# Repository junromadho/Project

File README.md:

Project
=======

It contains jun romadho's project free to share

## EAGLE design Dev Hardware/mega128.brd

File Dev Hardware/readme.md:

ini project bebas, temanya development board atmega128

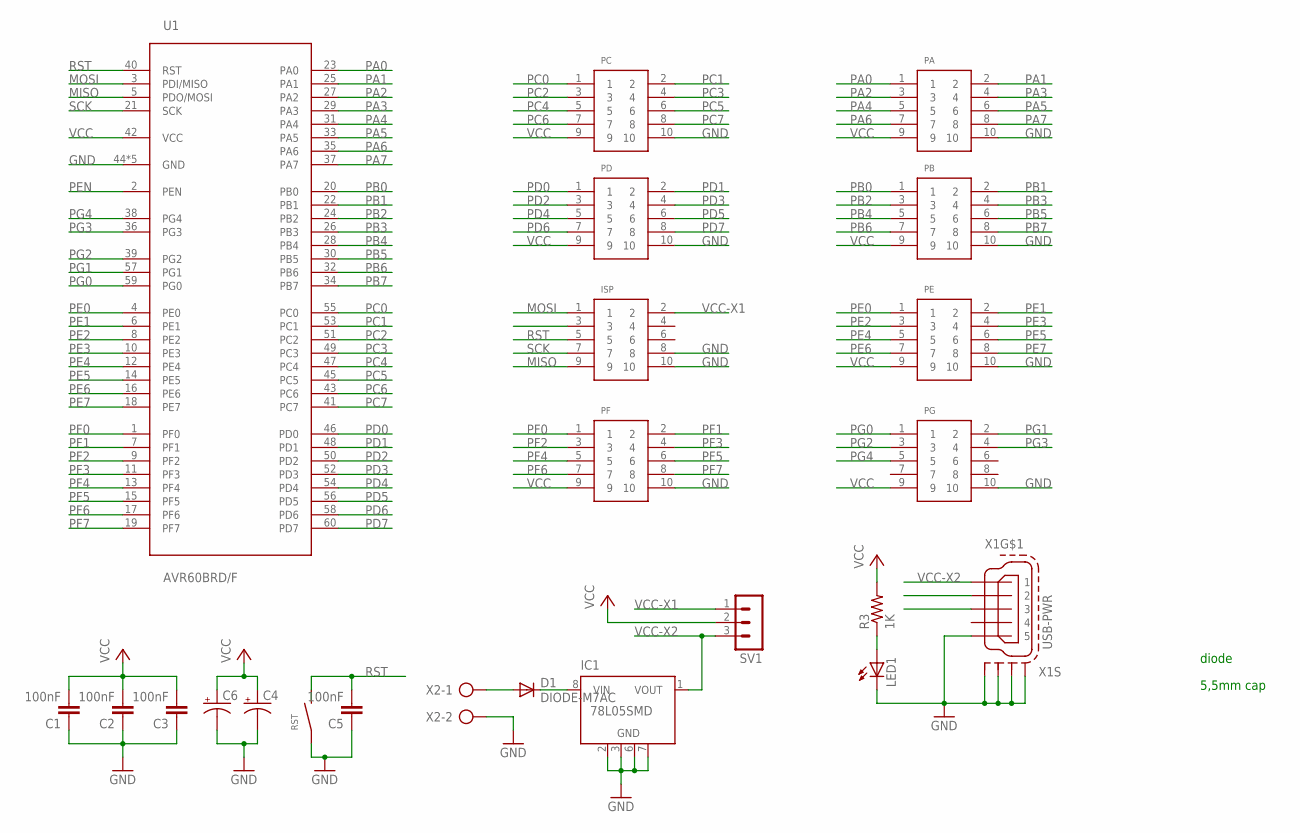
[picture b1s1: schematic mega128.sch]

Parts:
C1, C2, C3, C5: 100nF; C0805
C4, C6: CPOL-US085CS-1AR; 085CS_1AR
D1: DIODE-M7AC; M7
IC1: 78L05SMD; SO08
ISP: IDC-SOCK
LED1: LEDSML0805; SML0805
PA: IDC-SOCK
PB: IDC-SOCK
PC: IDC-SOCK
PD: IDC-SOCK
PE: IDC-SOCK
PF: IDC-SOCK
PG: IDC-SOCK
R3: 1K; R0805
RST: SMD-BTN
SV1: MA03-1
U1: AVR60BRD/F; AVR60-BRD
X1: USB-PWR; 32005-201
X2: AK300/2

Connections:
GND: C1.1, C2.1, C3.1, C4.-, C5.1, C6.-, IC1.2 (GND), IC1.3 (GND), IC1.6 (GND), IC1.7 (GND), ISP.8, ISP.10, LED1.C, PA.10, PB.10, PC.10, PD.10, PE.10, PF.10, PG.10, RST.1, U1.44 (GND), U1.61 (GND), U1.62 (GND), U1.63 (GND), U1.64 (GND), X1.5, X1.M1 (S1), X1.M2 (S2), X1.M3 (S3), X1.M4 (S4), X2.2
MISO: ISP.9, U1.5 (PDO/MOSI)
MOSI: ISP.1, U1.3 (PDI/MISO)
unnamed: LED1.A, R3.1
unnamed: D1.2 (A), X2.1
unnamed: D1.1 (C), IC1.8 (VIN)
PA0: PA.1, U1.23 (PA0)
PA1: PA.2, U1.25 (PA1)
PA2: PA.3, U1.27 (PA2)
PA3: PA.4, U1.29 (PA3)
PA4: PA.5, U1.31 (PA4)
PA5: PA.6, U1.33 (PA5)
PA6: PA.7, U1.35 (PA6)
PA7: PA.8, U1.37 (PA7)
PB0: PB.1, U1.20 (PB0)
PB1: PB.2, U1.22 (PB1)
PB2: PB.3, U1.24 (PB2)
PB3: PB.4, U1.26 (PB3)
PB4: PB.5, U1.28 (PB4)
PB5: PB.6, U1.30 (PB5)
PB6: PB.7, U1.32 (PB6)
PB7: PB.8, U1.34 (PB7)
PC0: PC.1, U1.55 (PC0)
PC1: PC.2, U1.53 (PC1)
PC2: PC.3, U1.51 (PC2)
PC3: PC.4, U1.49 (PC3)
PC4: PC.5, U1.47 (PC4)
PC5: PC.6, U1.45 (PC5)
PC6: PC.7, U1.43 (PC6)
PC7: PC.8, U1.41 (PC7)
PD0: PD.1, U1.46 (PD0)
PD1: PD.2, U1.48 (PD1)
PD2: PD.3, U1.50 (PD2)
PD3: PD.4, U1.52 (PD3)
PD4: PD.5, U1.54 (PD4)
PD5: PD.6, U1.56 (PD5)
PD6: PD.7, U1.58 (PD6)
PD7: PD.8, U1.60 (PD7)
PE0: PE.1, U1.4 (PE0)
PE1: PE.2, U1.6 (PE1)
PE2: PE.3, U1.8 (PE2)
PE3: PE.4, U1.10 (PE3)
PE4: PE.5, U1.12 (PE4)
PE5: PE.6, U1.14 (PE5)
PE6: PE.7, U1.16 (PE6)
PE7: PE.8, U1.18 (PE7)
PEN: U1.2 (PEN)
PF0: PF.1, U1.1 (PF0)
PF1: PF.2, U1.7 (PF1)
PF2: PF.3, U1.9 (PF2)
PF3: PF.4, U1.11 (PF3)
PF4: PF.5, U1.13 (PF4)
PF5: PF.6, U1.15 (PF5)
PF6: PF.7, U1.17 (PF6)
PF7: PF.8, U1.19 (PF7)
PG0: PG.1, U1.59 (PG0)
PG1: PG.2, U1.57 (PG1)
PG2: PG.3, U1.39 (PG2)
PG3: PG.4, U1.36 (PG3)
PG4: PG.5, U1.38 (PG4)
RST: C5.2, ISP.5, RST.2, U1.40 (RST)
SCK: ISP.7, U1.21 (SCK)
VCC: C1.2, C2.2, C3.2, C4.+, C6.+, PA.9, PB.9, PC.9, PD.9, PE.9, PF.9, PG.9, R3.2, SV1.2, U1.42 (VCC)
VCC-X1: ISP.2, SV1.1
VCC-X2: IC1.1 (VOUT), SV1.3, X1.1

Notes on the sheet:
5,5mm cap
diode

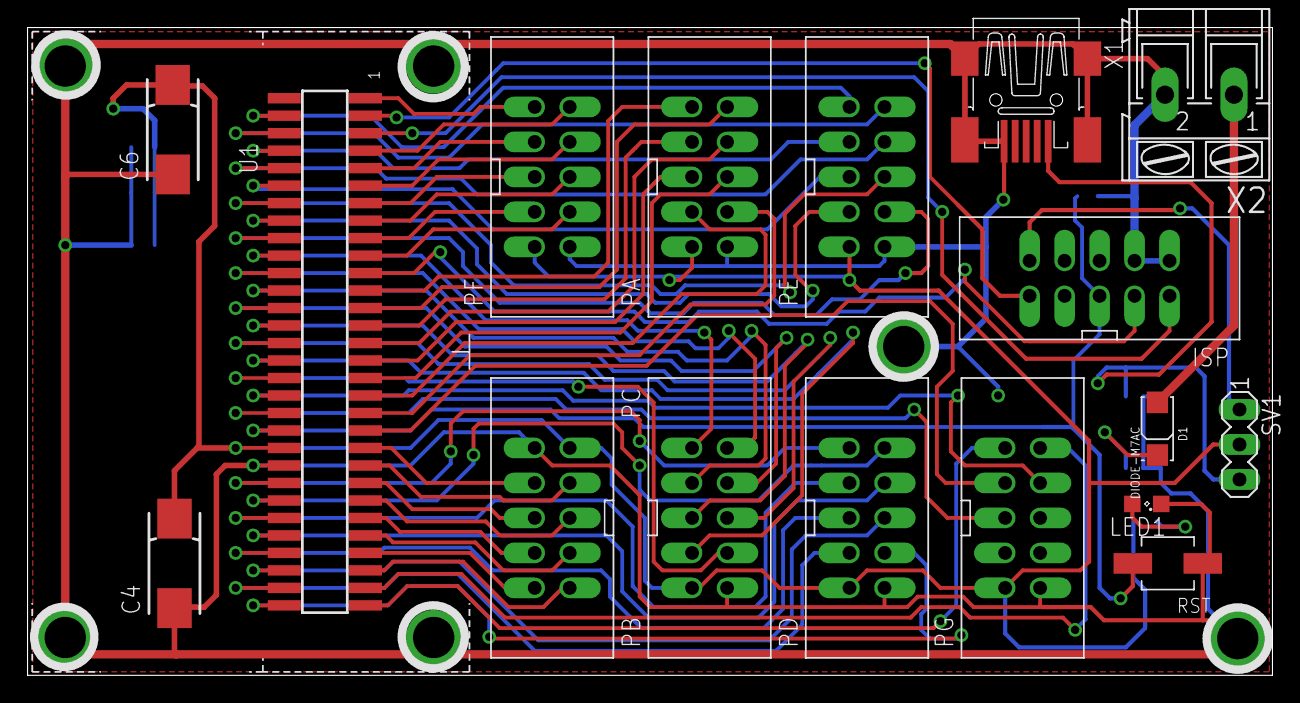
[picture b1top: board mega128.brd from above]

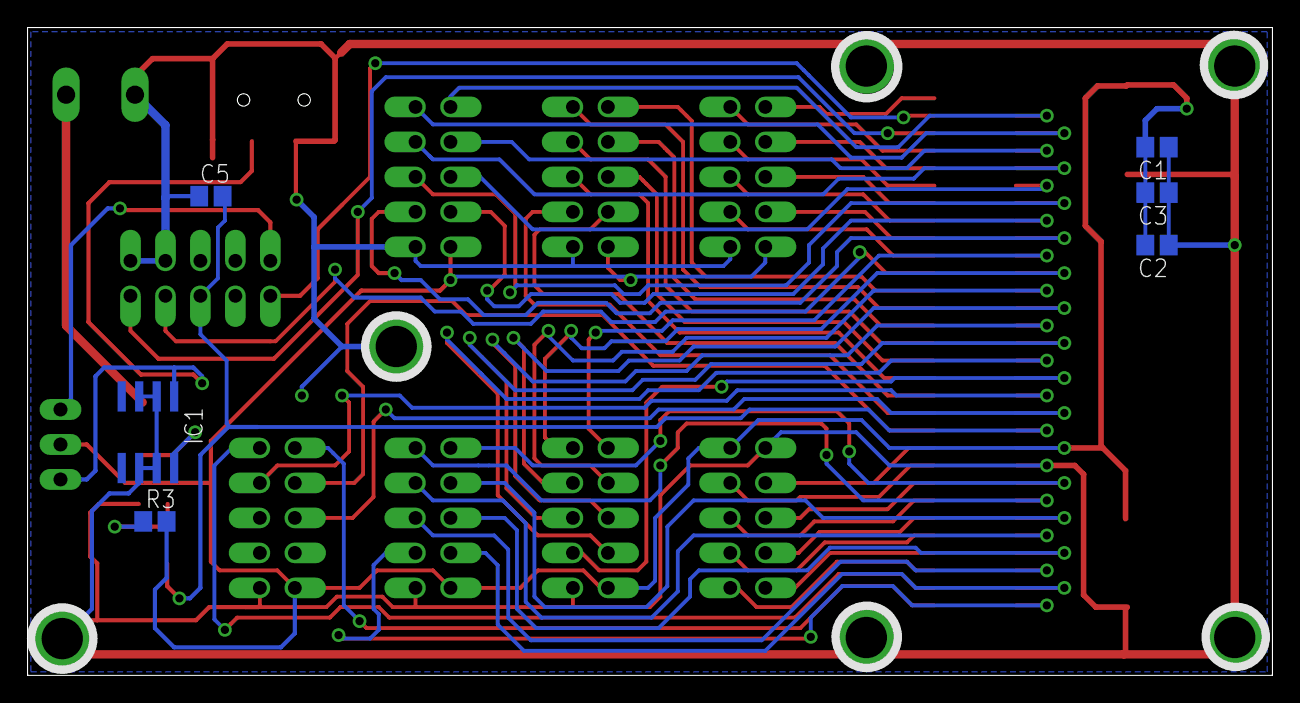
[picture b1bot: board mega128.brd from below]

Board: 2 copper layers, 90.4 x 47.0 mm, 23 parts (6 on the bottom side), 64 nets.

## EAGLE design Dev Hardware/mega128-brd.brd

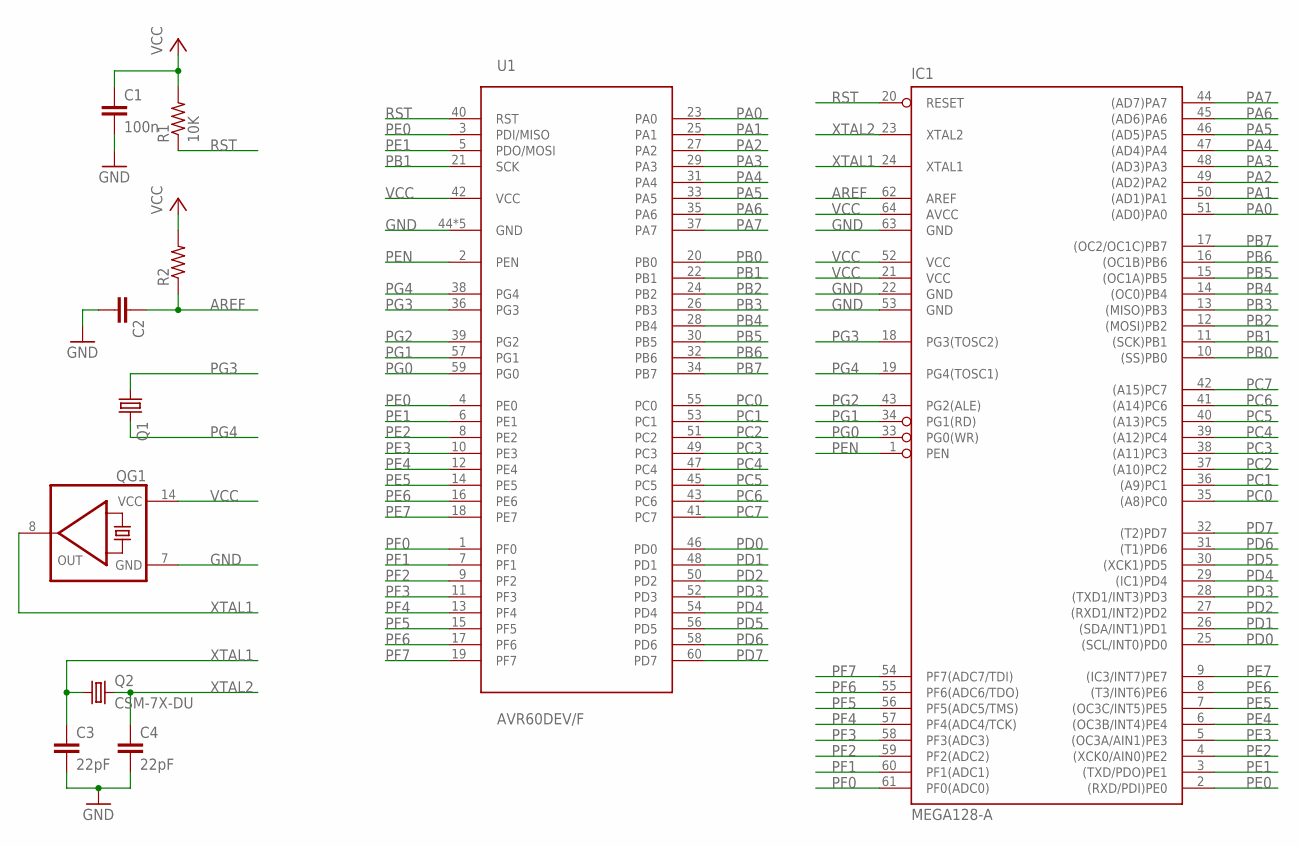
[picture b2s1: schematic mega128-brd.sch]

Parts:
C1: 100n; C0805
C2: C-EUC0805; C0805
C3, C4: 22pF; C0805
IC1: MEGA128-A; TQFP64
Q1: CRYSTALTC26V; TC26V
Q2: CSM-7X-DU
QG1: QG5860; DIL14S
R1: 10K; R0805
R2: R-US_R0805; R0805
U1: AVR60DEV/F; AVR60-DEV

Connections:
AREF: C2.1, IC1.62 (AREF), R2.1
GND: C1.2, C2.2, C3.2, C4.2, IC1.22 (GND), IC1.53 (GND), IC1.63 (GND), QG1.7 (GND), U1.44 (GND), U1.61 (GND), U1.62 (GND), U1.63 (GND), U1.64 (GND)
PA0: IC1.51 ((AD0)PA0), U1.23 (PA0)
PA1: IC1.50 ((AD1)PA1), U1.25 (PA1)
PA2: IC1.49 ((AD2)PA2), U1.27 (PA2)
PA3: IC1.48 ((AD3)PA3), U1.29 (PA3)
PA4: IC1.47 ((AD4)PA4), U1.31 (PA4)
PA5: IC1.46 ((AD5)PA5), U1.33 (PA5)
PA6: IC1.45 ((AD6)PA6), U1.35 (PA6)
PA7: IC1.44 ((AD7)PA7), U1.37 (PA7)
PB0: IC1.10 ((SS)PB0), U1.20 (PB0)
PB1: IC1.11 ((SCK)PB1), U1.21 (SCK), U1.22 (PB1)
PB2: IC1.12 ((MOSI)PB2), U1.24 (PB2)
PB3: IC1.13 ((MISO)PB3), U1.26 (PB3)
PB4: IC1.14 ((OC0)PB4), U1.28 (PB4)
PB5: IC1.15 ((OC1A)PB5), U1.30 (PB5)
PB6: IC1.16 ((OC1B)PB6), U1.32 (PB6)
PB7: IC1.17 ((OC2/OC1C)PB7), U1.34 (PB7)
PC0: IC1.35 ((A8)PC0), U1.55 (PC0)
PC1: IC1.36 ((A9)PC1), U1.53 (PC1)
PC2: IC1.37 ((A10)PC2), U1.51 (PC2)
PC3: IC1.38 ((A11)PC3), U1.49 (PC3)
PC4: IC1.39 ((A12)PC4), U1.47 (PC4)
PC5: IC1.40 ((A13)PC5), U1.45 (PC5)
PC6: IC1.41 ((A14)PC6), U1.43 (PC6)
PC7: IC1.42 ((A15)PC7), U1.41 (PC7)
PD0: IC1.25 ((SCL/INT0)PD0), U1.46 (PD0)
PD1: IC1.26 ((SDA/INT1)PD1), U1.48 (PD1)
PD2: IC1.27 ((RXD1/INT2)PD2), U1.50 (PD2)
PD3: IC1.28 ((TXD1/INT3)PD3), U1.52 (PD3)
PD4: IC1.29 ((IC1)PD4), U1.54 (PD4)
PD5: IC1.30 ((XCK1)PD5), U1.56 (PD5)
PD6: IC1.31 ((T1)PD6), U1.58 (PD6)
PD7: IC1.32 ((T2)PD7), U1.60 (PD7)
PE0: IC1.2 ((RXD/PDI)PE0), U1.3 (PDI/MISO), U1.4 (PE0)
PE1: IC1.3 ((TXD/PDO)PE1), U1.5 (PDO/MOSI), U1.6 (PE1)
PE2: IC1.4 ((XCK0/AIN0)PE2), U1.8 (PE2)
PE3: IC1.5 ((OC3A/AIN1)PE3), U1.10 (PE3)
PE4: IC1.6 ((OC3B/INT4)PE4), U1.12 (PE4)
PE5: IC1.7 ((OC3C/INT5)PE5), U1.14 (PE5)
PE6: IC1.8 ((T3/INT6)PE6), U1.16 (PE6)
PE7: IC1.9 ((IC3/INT7)PE7), U1.18 (PE7)
PEN: IC1.1 (PEN), U1.2 (PEN)
PF0: IC1.61 (PF0(ADC0)), U1.1 (PF0)
PF1: IC1.60 (PF1(ADC1)), U1.7 (PF1)
PF2: IC1.59 (PF2(ADC2)), U1.9 (PF2)
PF3: IC1.58 (PF3(ADC3)), U1.11 (PF3)
PF4: IC1.57 (PF4(ADC4/TCK)), U1.13 (PF4)
PF5: IC1.56 (PF5(ADC5/TMS)), U1.15 (PF5)
PF6: IC1.55 (PF6(ADC6/TDO)), U1.17 (PF6)
PF7: IC1.54 (PF7(ADC7/TDI)), U1.19 (PF7)
PG0: IC1.33 (PG0(WR)), U1.59 (PG0)
PG1: IC1.34 (PG1(RD)), U1.57 (PG1)
PG2: IC1.43 (PG2(ALE)), U1.39 (PG2)
PG3: IC1.18 (PG3(TOSC2)), Q1.1, U1.36 (PG3)
PG4: IC1.19 (PG4(TOSC1)), Q1.2, U1.38 (PG4)
RST: IC1.20 (RESET), R1.1, U1.40 (RST)
VCC: C1.1, IC1.21 (VCC), IC1.52 (VCC), IC1.64 (AVCC), QG1.14 (VCC), R1.2, R2.2, U1.42 (VCC)
XTAL1: C3.1, IC1.24 (XTAL1), Q2.1, QG1.8 (OUT)
XTAL2: C4.1, IC1.23 (XTAL2), Q2.2

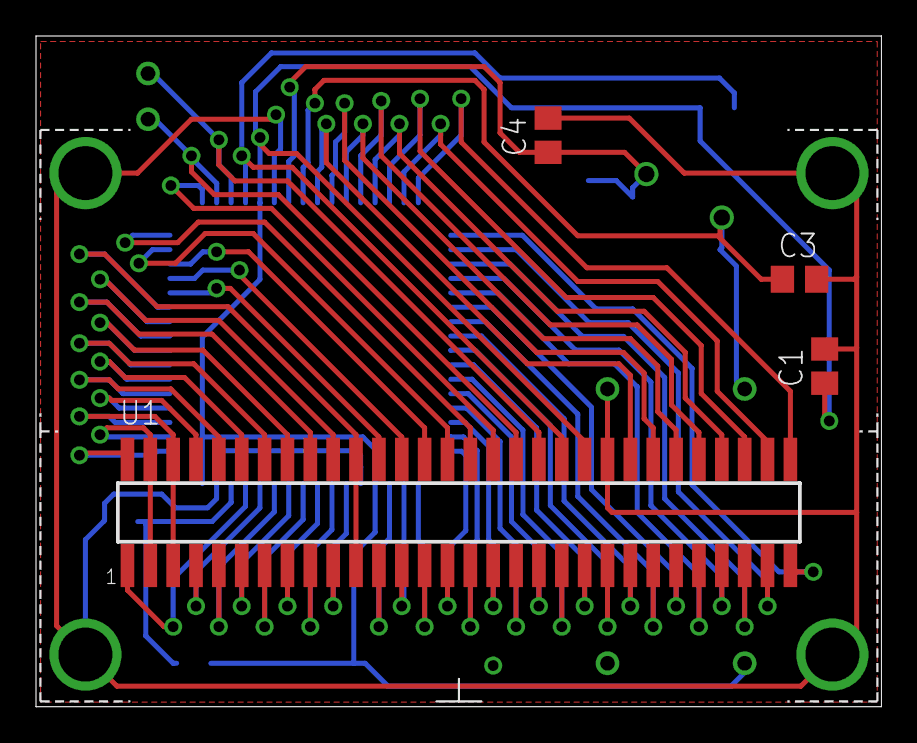
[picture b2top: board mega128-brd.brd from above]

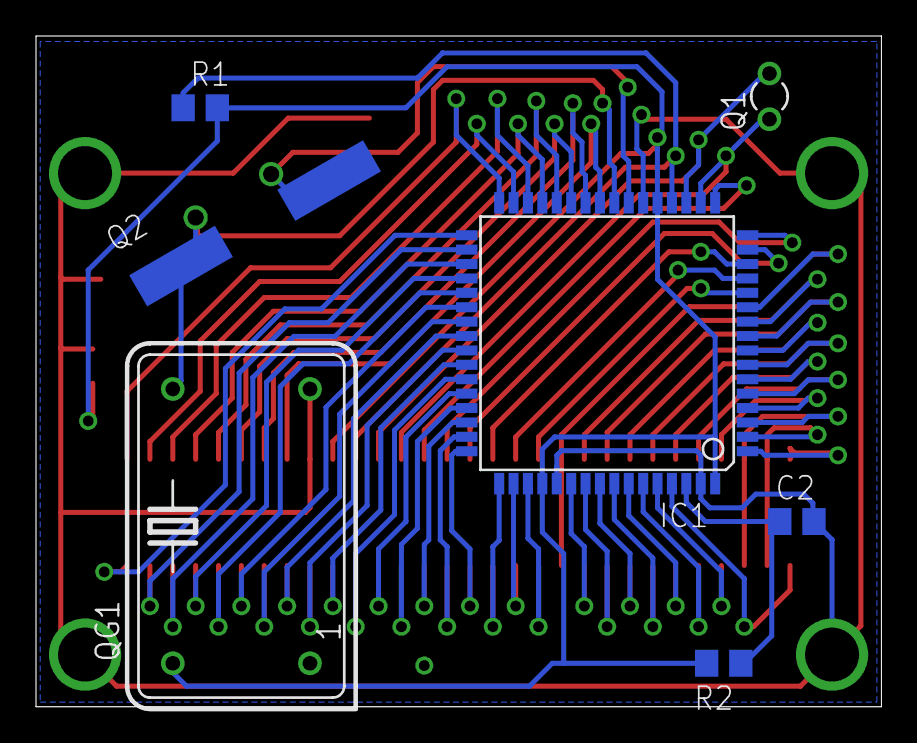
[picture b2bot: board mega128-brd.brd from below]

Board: 2 copper layers, 47.0 x 37.3 mm, 11 parts (7 on the bottom side), 60 nets.

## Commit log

2022-03-08 Add files via upload
    universal development board for atmega128 microcontroller.
2022-03-08 Add files via upload
    pic for atmega128
2022-03-08 Create readme.md
    just share
2022-03-08 Rename mega128-brd.brd to Dev Hardware/mega128-brd.brd
2022-03-08 Rename mega128-brd.sch to Dev Hardware/mega128-brd.sch
2022-03-08 Rename mega128.brd to Dev Hardware/mega128.brd
2022-03-08 Rename mega128.sch to Dev Hardware/mega128.sch
